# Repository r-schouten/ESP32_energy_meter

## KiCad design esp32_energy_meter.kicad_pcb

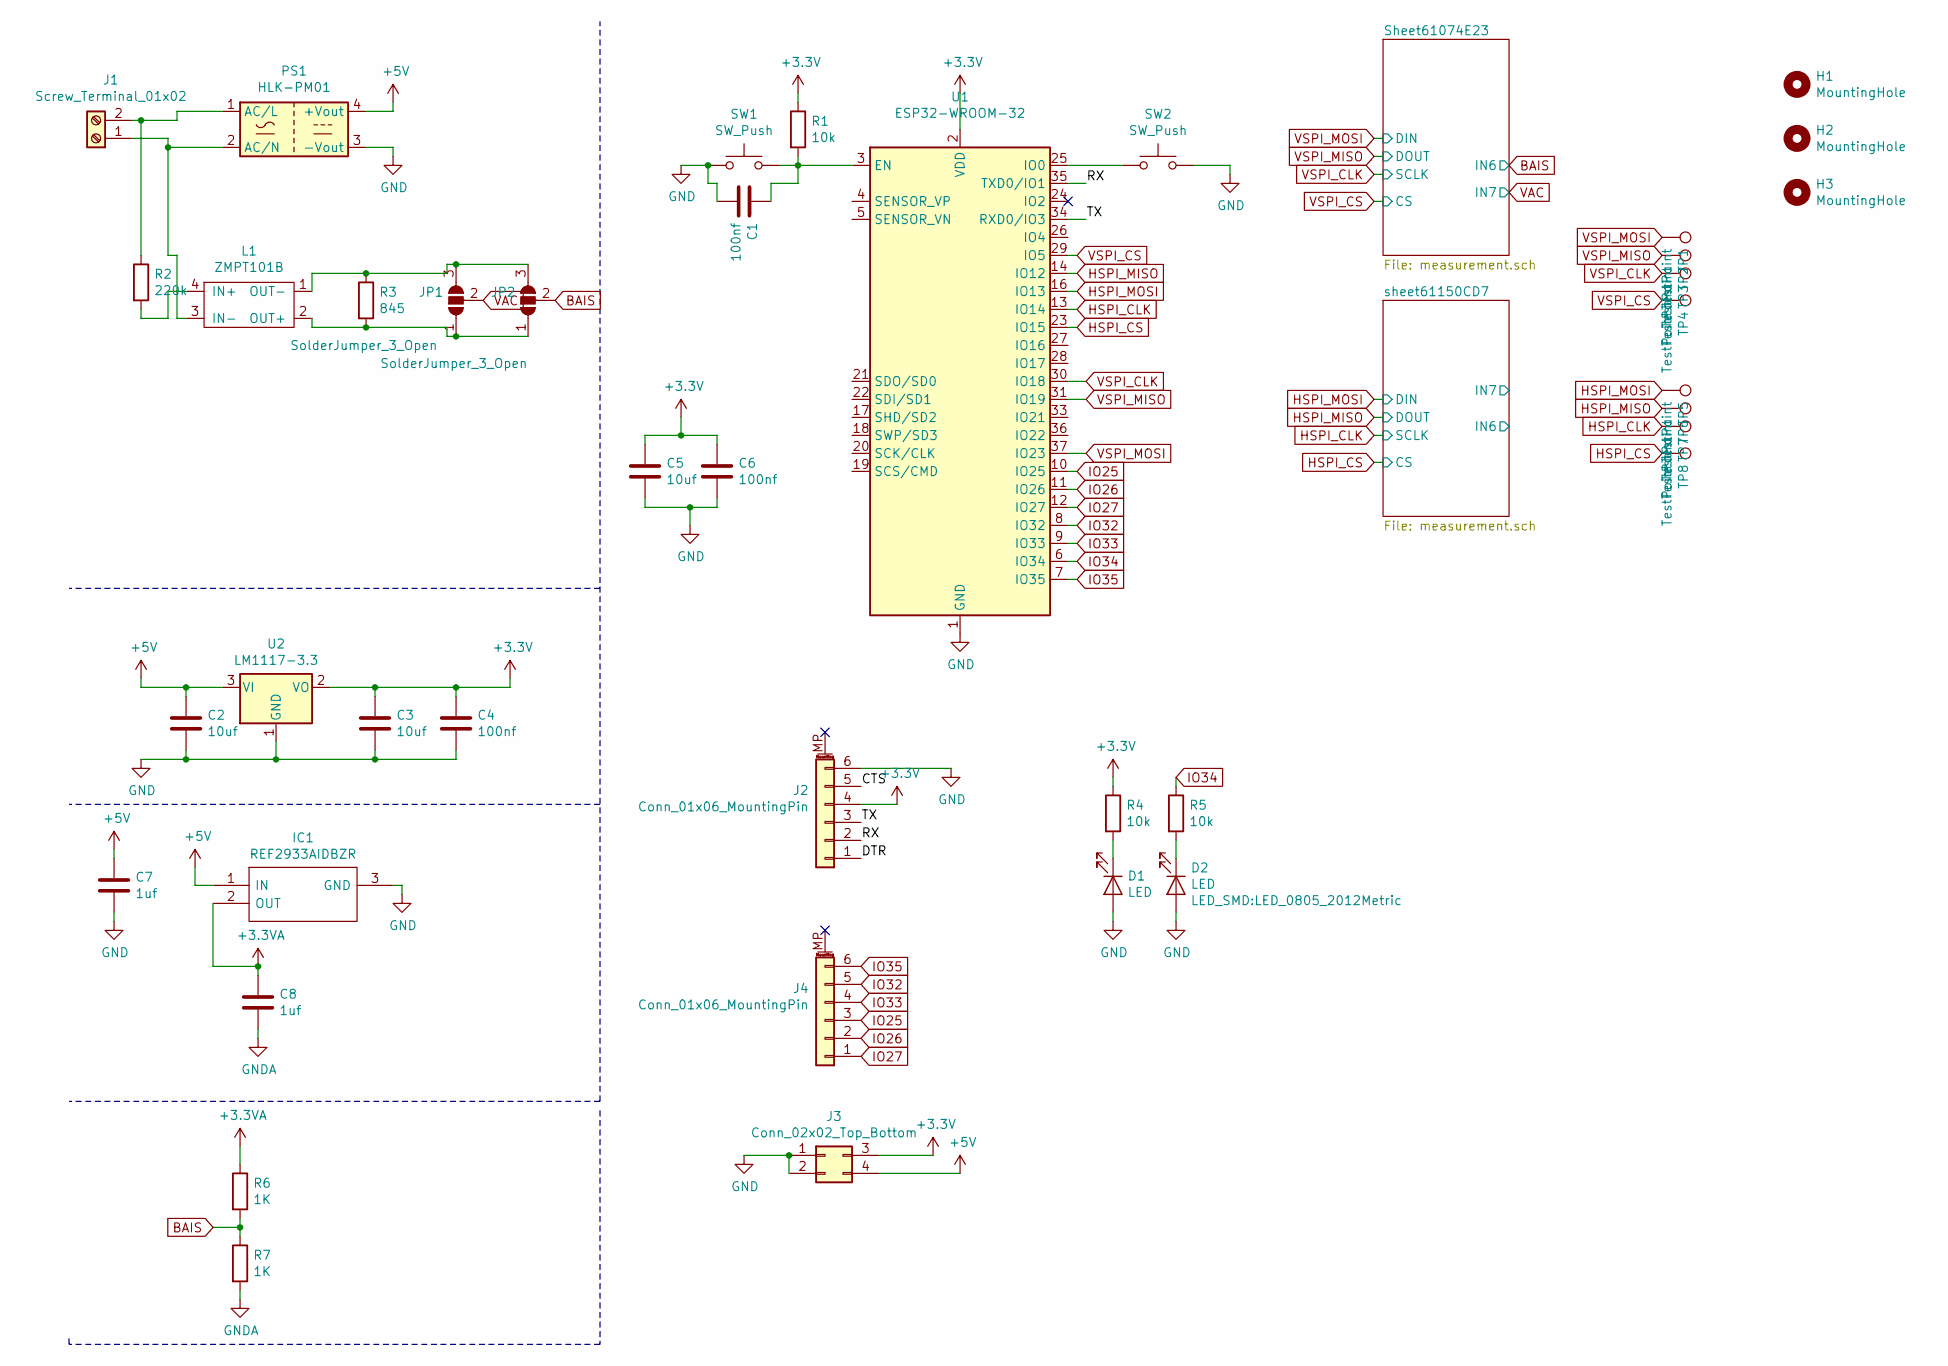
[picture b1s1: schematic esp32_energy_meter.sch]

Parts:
C1, C4, C6: 100nf; C_0805_2012Metric_Pad1.15x1.40mm_HandSolder; LCSC C62912
C2, C3, C5: 10uf; C_0805_2012Metric_Pad1.15x1.40mm_HandSolder; LCSC C90544
C7, C8: 1uf; C_0805_2012Metric_Pad1.15x1.40mm_HandSolder; LCSC C215803
D1, D2: LED; LED_0805_2012Metric; LCSC C131244
H1, H2, H3: MountingHole; MountingHole_3.2mm_M3; LCSC x
IC1: REF2933AIDBZR; SOT95P237X112-3N; Mouser Part Number 595-REF2933AIDBZR
J1: Screw_Terminal_01x02; TerminalBlock_bornier-2_P5.08mm; LCSC C8269
J2, J4: Conn_01x06_MountingPin; PinHeader_1x06_P2.54mm_Vertical; LCSC x
J3: Conn_02x02_Top_Bottom; PinHeader_2x02_P2.54mm_Vertical; LCSC x
JP1, JP2: SolderJumper_3_Open; SolderJumper-3_P1.3mm_Open_RoundedPad1.0x1.5mm; LCSC x
L1: ZMPT101B; LCSC C111858
PS1: HLK-PM01; Converter_ACDC_HiLink_HLK-PMxx; LCSC C209903
R1, R4, R5: 10k; R_0805_2012Metric; LCSC C25612
R2: 220k; R_2512_6332Metric; LCSC C175527
R3: 845; R_0805_2012Metric; LCSC C425484
R6, R7: 1K; R_0805_2012Metric; LCSC C95781
SW1, SW2: SW_Push; K2-1107ST; LCSC x
TP1, TP2, TP3, TP4, TP5, TP6, TP7, TP8: TestPoint; TestPoint_Pad_1.0x1.0mm; LCSC x
U1: ESP32-WROOM-32; LCSC C82899
U2: LM1117-3.3; SOT-223; LCSC C23984

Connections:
+3.3VA: C8.1, IC1.2 (OUT), R6.1; also elsewhere on the board
+3V3: C3.1, C4.1, C5.1, C6.1, J2.4, J3.3, R1.1, R4.1, U1.2 (VDD), U2.2 (VO); also elsewhere on the board
+5V: C2.1, C7.1, IC1.1 (IN), J3.4, PS1.4 (+Vout), U2.3 (VI)
/CTS: J2.5
/DTR: J2.1
/RX: J2.2, U1.35 (TXD0/IO1)
/TX: J2.3, U1.34 (RXD0/IO3)
BAIS: JP2.2 (C), R6.2, R7.1; also elsewhere on the board
GND: C1.2, C2.2, C3.2, C4.2, C5.2, C6.2, C7.2, D1.2 (A), D2.2 (A), IC1.3 (GND), J2.6, J3.1, J3.2, PS1.3 (-Vout), SW1.1, SW2.2, U1.1 (GND), U1.15 (GND), U1.38 (GND), U1.39 (GND), U2.1 (GND); also elsewhere on the board
GNDA: C8.2, R7.2; also elsewhere on the board
HSPI_CLK: TP7.1, U1.13 (IO14); also elsewhere on the board
HSPI_CS: TP8.1, U1.23 (IO15); also elsewhere on the board
HSPI_MISO: TP6.1, U1.14 (IO12); also elsewhere on the board
HSPI_MOSI: TP5.1, U1.16 (IO13); also elsewhere on the board
IO25: J4.3, U1.10 (IO25)
IO26: J4.2, U1.11 (IO26)
IO27: J4.1, U1.12 (IO27)
IO32: J4.5, U1.8 (IO32)
IO33: J4.4, U1.9 (IO33)
IO34: R5.1, U1.6 (IO34)
IO35: J4.6, U1.7 (IO35)
unnamed: C1.1, R1.2, SW1.2, U1.3 (EN)
unnamed: D1.1 (K), R4.2
unnamed: D2.1 (K), R5.2
unnamed: J1.1, L1.3 (IN-), PS1.2 (AC/N)
unnamed: J1.2, PS1.1 (AC/L), R2.1
unnamed: JP1.1 (A), JP2.1 (A), L1.2 (OUT+), R3.2
unnamed: JP1.3 (B), JP2.3 (B), L1.1 (OUT-), R3.1
unnamed: L1.4 (IN+), R2.2
unnamed: SW2.1, U1.25 (IO0)
VAC: JP1.2 (C); also elsewhere on the board
VSPI_CLK: TP3.1, U1.30 (IO18); also elsewhere on the board
VSPI_CS: TP4.1, U1.29 (IO5); also elsewhere on the board
VSPI_MISO: TP2.1, U1.31 (IO19); also elsewhere on the board
VSPI_MOSI: TP1.1, U1.37 (IO23); also elsewhere on the board

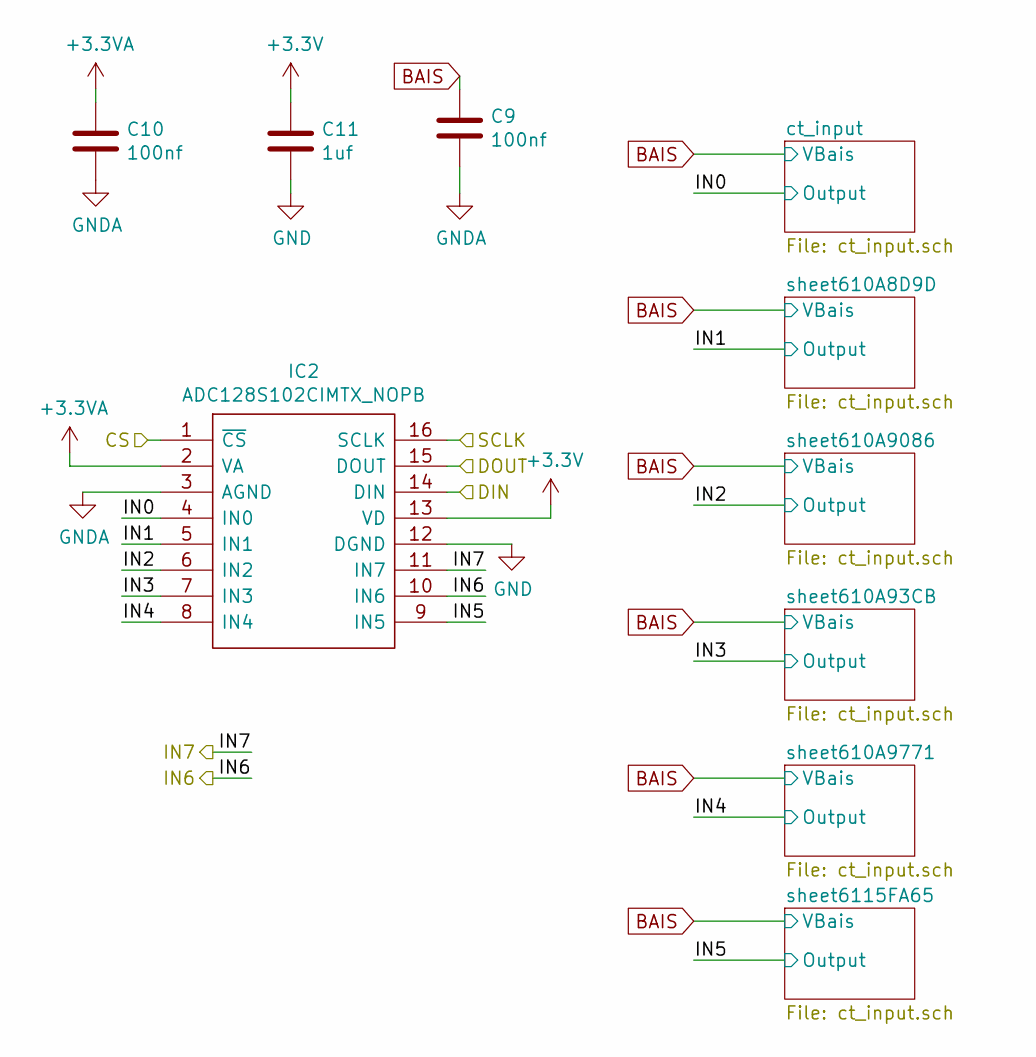
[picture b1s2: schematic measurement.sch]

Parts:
C12, C13: 100nf; C_0805_2012Metric_Pad1.15x1.40mm_HandSolder; LCSC C62912
C14: 1uf; C_0805_2012Metric_Pad1.15x1.40mm_HandSolder; LCSC C215803
IC3: ADC128S102CIMTX_NOPB; SOP65P640X120-16N; Mouser Part Number 926-A128S102CIMTXNPB

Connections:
+3.3VA: C13.1, IC3.2 (VA); also elsewhere on the board
+3V3: C14.1, IC3.13 (VD); also elsewhere on the board
/Sheet61074E23/IN0: IC3.4 (IN0); also elsewhere on the board
/Sheet61074E23/IN1: IC3.5 (IN1); also elsewhere on the board
/Sheet61074E23/IN2: IC3.6 (IN2); also elsewhere on the board
/Sheet61074E23/IN3: IC3.7 (IN3); also elsewhere on the board
/Sheet61074E23/IN4: IC3.8 (IN4); also elsewhere on the board
/Sheet61074E23/IN5: IC3.9 (IN5); also elsewhere on the board
BAIS: C12.1, IC3.10 (IN6); also elsewhere on the board
GND: C14.2, IC3.12 (DGND); also elsewhere on the board
GNDA: C12.2, C13.2, IC3.3 (AGND); also elsewhere on the board
VAC: IC3.11 (IN7); also elsewhere on the board
VSPI_CLK: IC3.16 (SCLK); also elsewhere on the board
VSPI_CS: IC3.1 (~CS); also elsewhere on the board
VSPI_MISO: IC3.15 (DOUT); also elsewhere on the board
VSPI_MOSI: IC3.14 (DIN); also elsewhere on the board

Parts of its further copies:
C9, C10: 100nf; C_0805_2012Metric_Pad1.15x1.40mm_HandSolder; LCSC C62912
C11: 1uf; C_0805_2012Metric_Pad1.15x1.40mm_HandSolder; LCSC C215803
IC2: ADC128S102CIMTX_NOPB; SOP65P640X120-16N; Mouser Part Number 926-A128S102CIMTXNPB

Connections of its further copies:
+3.3VA: C10.1, IC2.2 (VA); also elsewhere on the board
+3V3: C11.1, IC2.13 (VD); also elsewhere on the board
/sheet61150CD7/IN0: IC2.4 (IN0); also elsewhere on the board
/sheet61150CD7/IN1: IC2.5 (IN1); also elsewhere on the board
/sheet61150CD7/IN2: IC2.6 (IN2); also elsewhere on the board
/sheet61150CD7/IN3: IC2.7 (IN3); also elsewhere on the board
/sheet61150CD7/IN4: IC2.8 (IN4); also elsewhere on the board
/sheet61150CD7/IN5: IC2.9 (IN5); also elsewhere on the board
/sheet61150CD7/IN6: IC2.10 (IN6)
/sheet61150CD7/IN7: IC2.11 (IN7)
BAIS: C9.1; also elsewhere on the board
GND: C11.2, IC2.12 (DGND); also elsewhere on the board
GNDA: C9.2, C10.2, IC2.3 (AGND); also elsewhere on the board
HSPI_CLK: IC2.16 (SCLK); also elsewhere on the board
HSPI_CS: IC2.1 (~CS); also elsewhere on the board
HSPI_MISO: IC2.15 (DOUT); also elsewhere on the board
HSPI_MOSI: IC2.14 (DIN); also elsewhere on the board

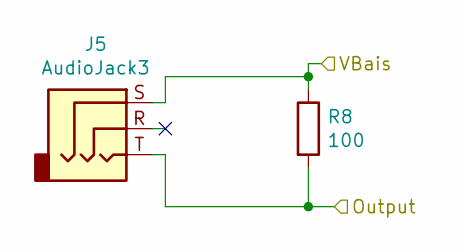
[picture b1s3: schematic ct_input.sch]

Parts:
J11: AudioJack3; C18594; LCSC C18594
R14: 100; R_0805_2012Metric; LCSC C478885

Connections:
/Sheet61074E23/IN0: J11.T, R14.2; also elsewhere on the board
BAIS: J11.S, R14.1; also elsewhere on the board

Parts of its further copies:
J5, J6, J7, J8, J9, J10, J12, J13, J14, J15, J16: AudioJack3; C18594; LCSC C18594
R8, R9, R10, R11, R12, R13, R15, R16, R17, R18, R19: 100; R_0805_2012Metric; LCSC C478885

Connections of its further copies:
/Sheet61074E23/IN1: J12.T, R15.2; also elsewhere on the board
/Sheet61074E23/IN2: J13.T, R16.2; also elsewhere on the board
/Sheet61074E23/IN3: J14.T, R17.2; also elsewhere on the board
/Sheet61074E23/IN4: J15.T, R18.2; also elsewhere on the board
/Sheet61074E23/IN5: J16.T, R19.2; also elsewhere on the board
/sheet61150CD7/IN0: J5.T, R8.2; also elsewhere on the board
/sheet61150CD7/IN1: J6.T, R9.2; also elsewhere on the board
/sheet61150CD7/IN2: J7.T, R10.2; also elsewhere on the board
/sheet61150CD7/IN3: J8.T, R11.2; also elsewhere on the board
/sheet61150CD7/IN4: J9.T, R12.2; also elsewhere on the board
/sheet61150CD7/IN5: J10.T, R13.2; also elsewhere on the board
BAIS: J5.S, J6.S, J7.S, J8.S, J9.S, J10.S, J12.S, J13.S, J14.S, J15.S, J16.S, R8.1, R9.1, R10.1, R11.1, R12.1, R13.1, R15.1, R16.1, R17.1, R18.1, R19.1; also elsewhere on the board

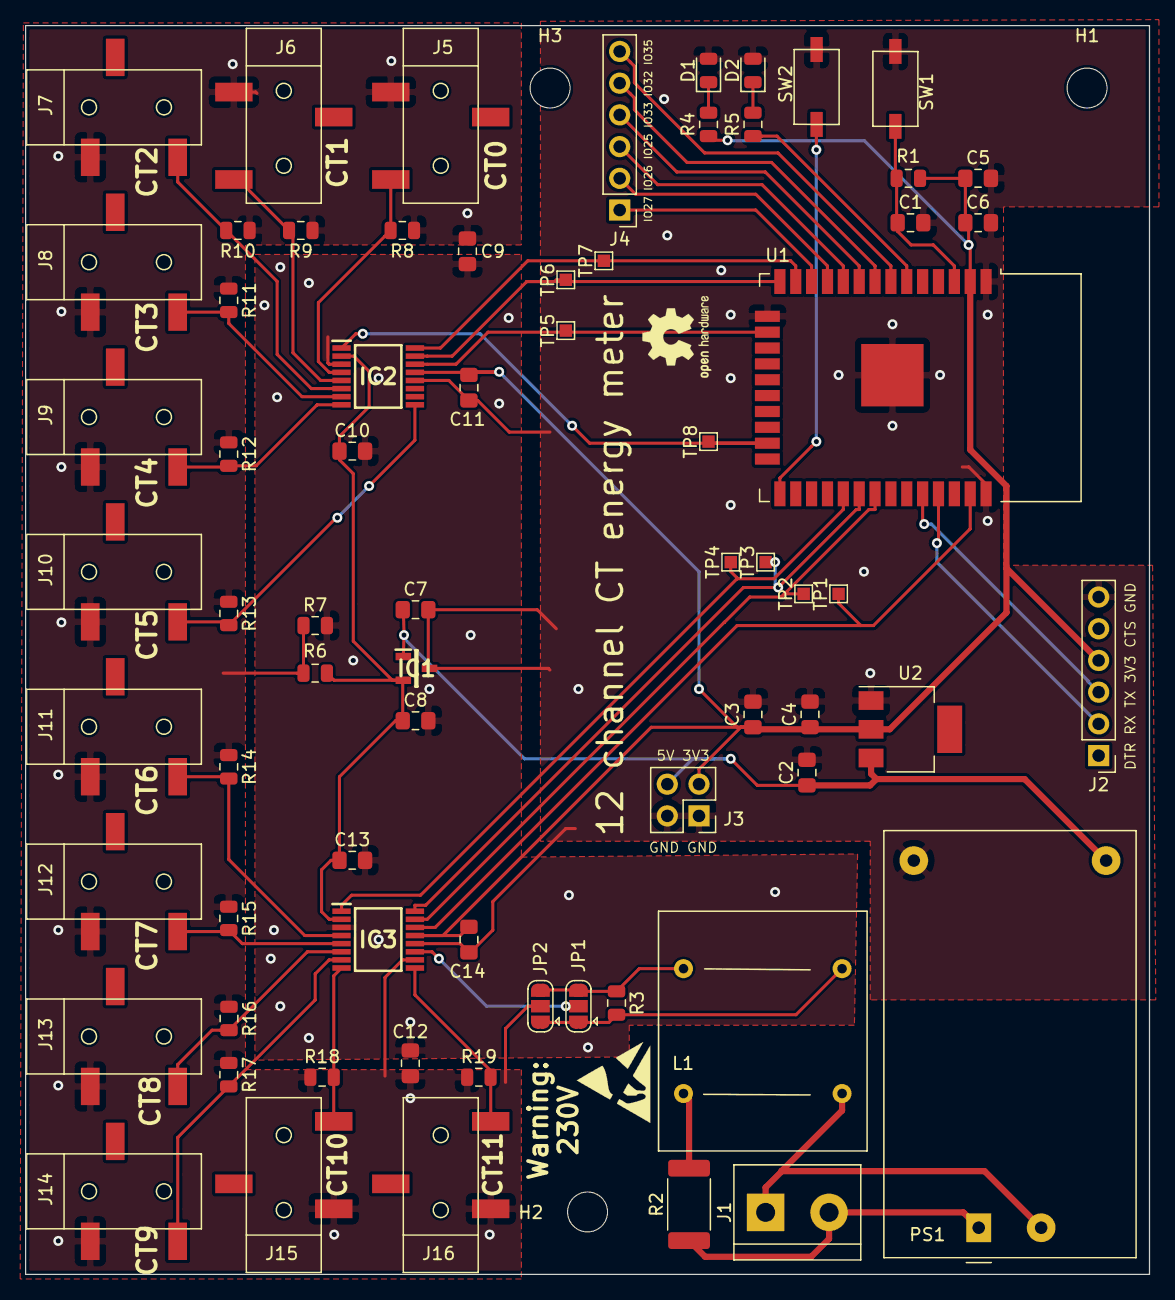
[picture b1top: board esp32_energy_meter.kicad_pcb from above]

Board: 2 copper layers, 90.0 x 100.0 mm, 73 parts (0 on the bottom side), 45 nets.

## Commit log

2021-07-30 little modifications
